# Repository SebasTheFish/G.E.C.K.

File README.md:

# Project G.E.C.K. (Garden of Eden Creation Kit)

## Overview

This project focuses around the creation of a cost-effective and flexible solution for the automation and control of various greenhouse processes.

## Goals

* Insert
* List
* Of
* Goals
* Here

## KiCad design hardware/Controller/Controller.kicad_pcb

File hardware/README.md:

# Hardware

The hardware folder can be used to store any files and documentation relating to the physical design of the hardware (gerber files, image assets, BOMs, etc.) This folder will need to be partitioned by board to keep organized.

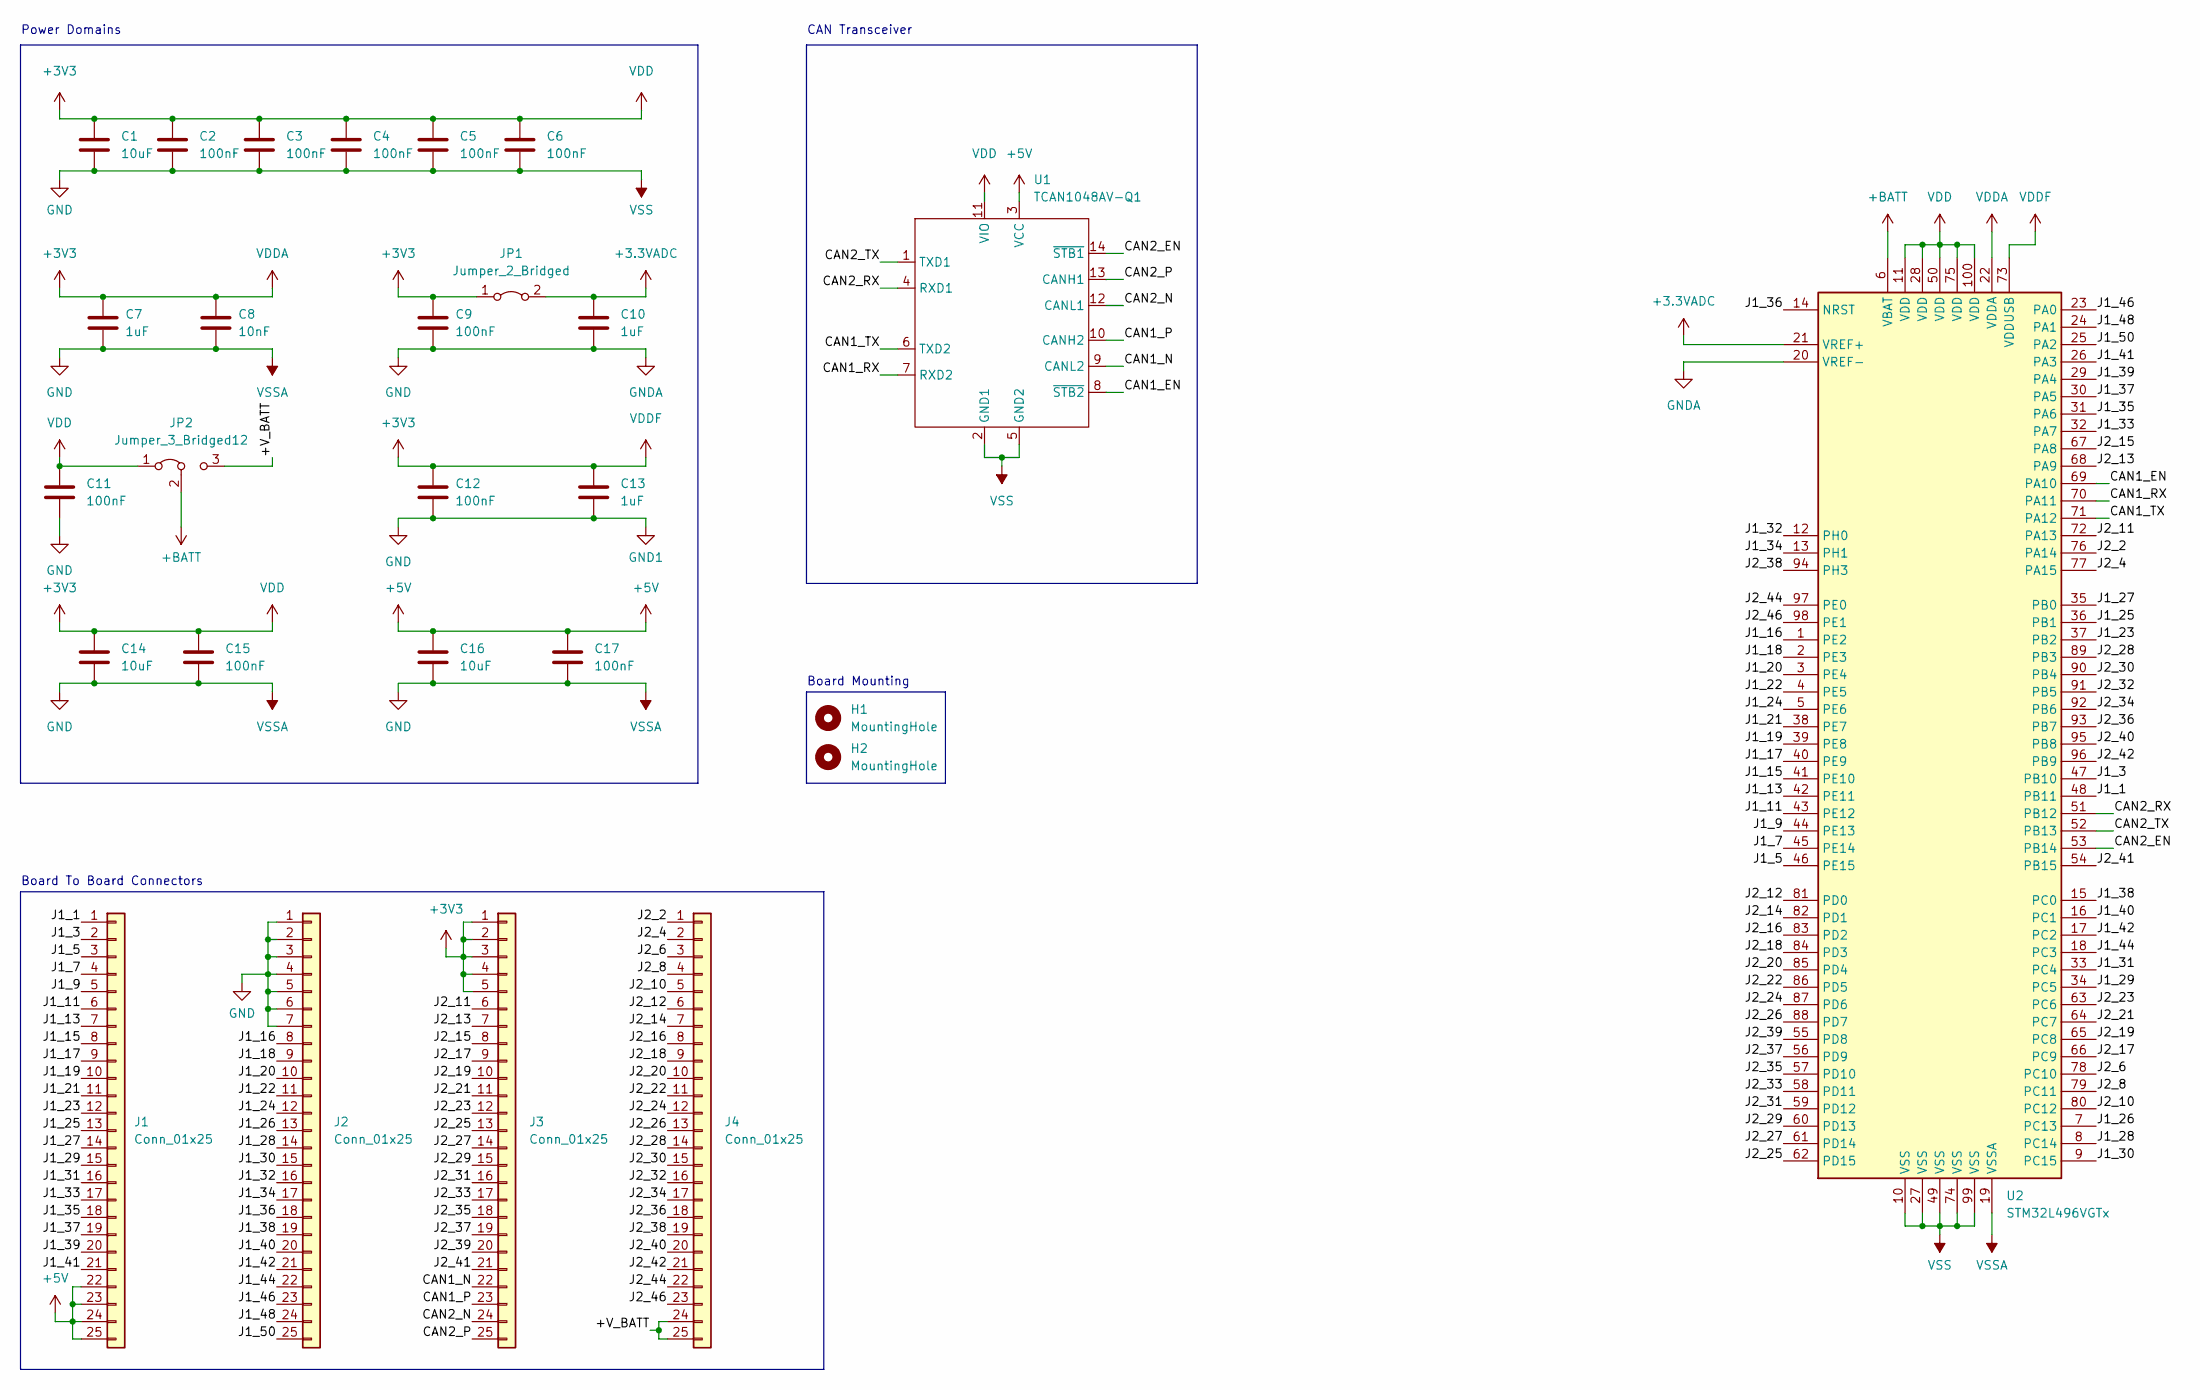
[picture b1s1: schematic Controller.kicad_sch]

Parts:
C1, C14, C16: 10uF; C_0603_1608Metric
C2, C3, C4, C5, C6, C9, C11, C12, C15, C17: 100nF; C_0603_1608Metric
C7, C10, C13: 1uF; C_0603_1608Metric
C8: 10nF; C_0603_1608Metric
H1, H2: MountingHole; MountingHole_3.2mm_M3
J1, J2, J3, J4: Conn_01x25; PinHeader_1x25_P1.00mm_Vertical
JP1: Jumper_2_Bridged; SolderJumper-2_P1.3mm_Bridged_Pad1.0x1.5mm
JP2: Jumper_3_Bridged12; SolderJumper-3_P1.3mm_Bridged12_Pad1.0x1.5mm
U1: TCAN1048AV-Q1; SOIC-14_3.9x8.7mm_P1.27mm
U2: STM32L496VGTx; LQFP-100_14x14mm_P0.5mm

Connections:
+3.3VADC: C10.1, JP1.2 (B), U2.21 (VREF+)
+5V: C16.1, C17.1, J1.22, J1.23, J1.24, J1.25, U1.3 (VCC)
+BATT: JP2.2 (C), U2.6 (VBAT)
/+V_BATT: J4.24, J4.25, JP2.3 (B)
/CAN1_EN: U1.8 (~STB2), U2.69 (PA10)
/CAN1_N: J3.22, U1.9 (CANL2)
/CAN1_P: J3.23, U1.10 (CANH2)
/CAN1_RX: U1.7 (RXD2), U2.70 (PA11)
/CAN1_TX: U1.6 (TXD2), U2.71 (PA12)
/CAN2_EN: U1.14 (~STB1), U2.53 (PB14)
/CAN2_N: J3.24, U1.12 (CANL1)
/CAN2_P: J3.25, U1.13 (CANH1)
/CAN2_RX: U1.4 (RXD1), U2.51 (PB12)
/CAN2_TX: U1.1 (TXD1), U2.52 (PB13)
/J1_1: J1.1, U2.48 (PB11)
/J1_3: J1.2, U2.47 (PB10)
/J1_5: J1.3, U2.46 (PE15)
/J1_7: J1.4, U2.45 (PE14)
/J1_9: J1.5, U2.44 (PE13)
/J1_11: J1.6, U2.43 (PE12)
/J1_13: J1.7, U2.42 (PE11)
/J1_15: J1.8, U2.41 (PE10)
/J1_16: J2.8, U2.1 (PE2)
/J1_17: J1.9, U2.40 (PE9)
/J1_18: J2.9, U2.2 (PE3)
/J1_19: J1.10, U2.39 (PE8)
/J1_20: J2.10, U2.3 (PE4)
/J1_21: J1.11, U2.38 (PE7)
/J1_22: J2.11, U2.4 (PE5)
/J1_23: J1.12, U2.37 (PB2)
/J1_24: J2.12, U2.5 (PE6)
/J1_25: J1.13, U2.36 (PB1)
/J1_26: J2.13, U2.7 (PC13)
/J1_27: J1.14, U2.35 (PB0)
/J1_28: J2.14, U2.8 (PC14)
/J1_29: J1.15, U2.34 (PC5)
/J1_30: J2.15, U2.9 (PC15)
/J1_31: J1.16, U2.33 (PC4)
/J1_32: J2.16, U2.12 (PH0)
/J1_33: J1.17, U2.32 (PA7)
/J1_34: J2.17, U2.13 (PH1)
/J1_35: J1.18, U2.31 (PA6)
/J1_36: J2.18, U2.14 (NRST)
/J1_37: J1.19, U2.30 (PA5)
/J1_38: J2.19, U2.15 (PC0)
/J1_39: J1.20, U2.29 (PA4)
/J1_40: J2.20, U2.16 (PC1)
/J1_41: J1.21, U2.26 (PA3)
/J1_42: J2.21, U2.17 (PC2)
/J1_44: J2.22, U2.18 (PC3)
/J1_46: J2.23, U2.23 (PA0)
/J1_48: J2.24, U2.24 (PA1)
/J1_50: J2.25, U2.25 (PA2)
/J2_2: J4.1, U2.76 (PA14)
/J2_4: J4.2, U2.77 (PA15)
/J2_6: J4.3, U2.78 (PC10)
/J2_8: J4.4, U2.79 (PC11)
/J2_10: J4.5, U2.80 (PC12)
/J2_11: J3.6, U2.72 (PA13)
/J2_12: J4.6, U2.81 (PD0)
/J2_13: J3.7, U2.68 (PA9)
/J2_14: J4.7, U2.82 (PD1)
/J2_15: J3.8, U2.67 (PA8)
/J2_16: J4.8, U2.83 (PD2)
/J2_17: J3.9, U2.66 (PC9)
/J2_18: J4.9, U2.84 (PD3)
/J2_19: J3.10, U2.65 (PC8)
/J2_20: J4.10, U2.85 (PD4)
/J2_21: J3.11, U2.64 (PC7)
/J2_22: J4.11, U2.86 (PD5)
/J2_23: J3.12, U2.63 (PC6)
/J2_24: J4.12, U2.87 (PD6)
/J2_25: J3.13, U2.62 (PD15)
/J2_26: J4.13, U2.88 (PD7)
/J2_27: J3.14, U2.61 (PD14)
/J2_28: J4.14, U2.89 (PB3)
/J2_29: J3.15, U2.60 (PD13)
/J2_30: J4.15, U2.90 (PB4)
/J2_31: J3.16, U2.59 (PD12)
/J2_32: J4.16, U2.91 (PB5)
/J2_33: J3.17, U2.58 (PD11)
/J2_34: J4.17, U2.92 (PB6)
/J2_35: J3.18, U2.57 (PD10)
/J2_36: J4.18, U2.93 (PB7)
/J2_37: J3.19, U2.56 (PD9)
/J2_38: J4.19, U2.94 (PH3)
/J2_39: J3.20, U2.55 (PD8)
/J2_40: J4.20, U2.95 (PB8)
/J2_41: J3.21, U2.54 (PB15)
/J2_42: J4.21, U2.96 (PB9)
/J2_44: J4.22, U2.97 (PE0)
/J2_46: J4.23, U2.98 (PE1)
GND: C1.2, C2.2, C3.2, C4.2, C5.2, C6.2, C7.2, C8.2, C9.2, C10.2, C11.2, C12.2, C13.2, C14.2, C15.2, C16.2, C17.2, J2.1, J2.2, J2.3, J2.4, J2.5, J2.6, J2.7, U1.2 (GND1), U1.5 (GND2), U2.10 (VSS), U2.19 (VSSA), U2.20 (VREF-), U2.27 (VSS), U2.49 (VSS), U2.74 (VSS), U2.99 (VSS)

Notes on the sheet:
CAN Transceiver
Board Mounting
Power Domains
Board To Board Connectors

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
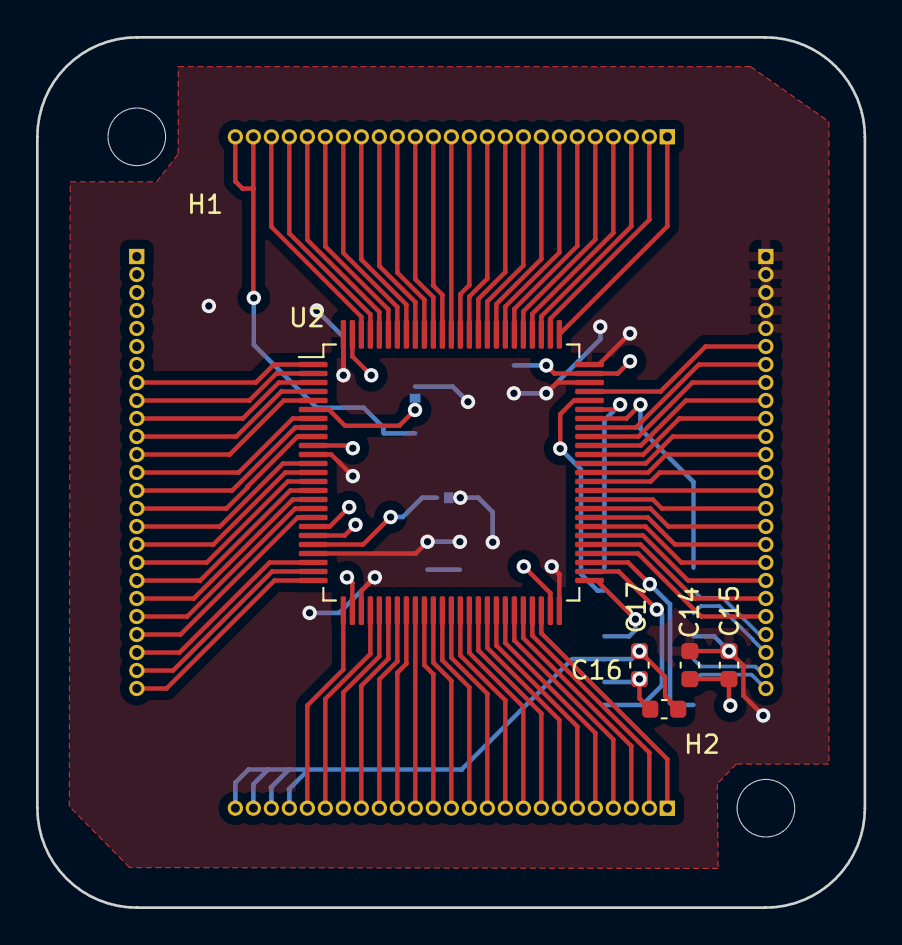
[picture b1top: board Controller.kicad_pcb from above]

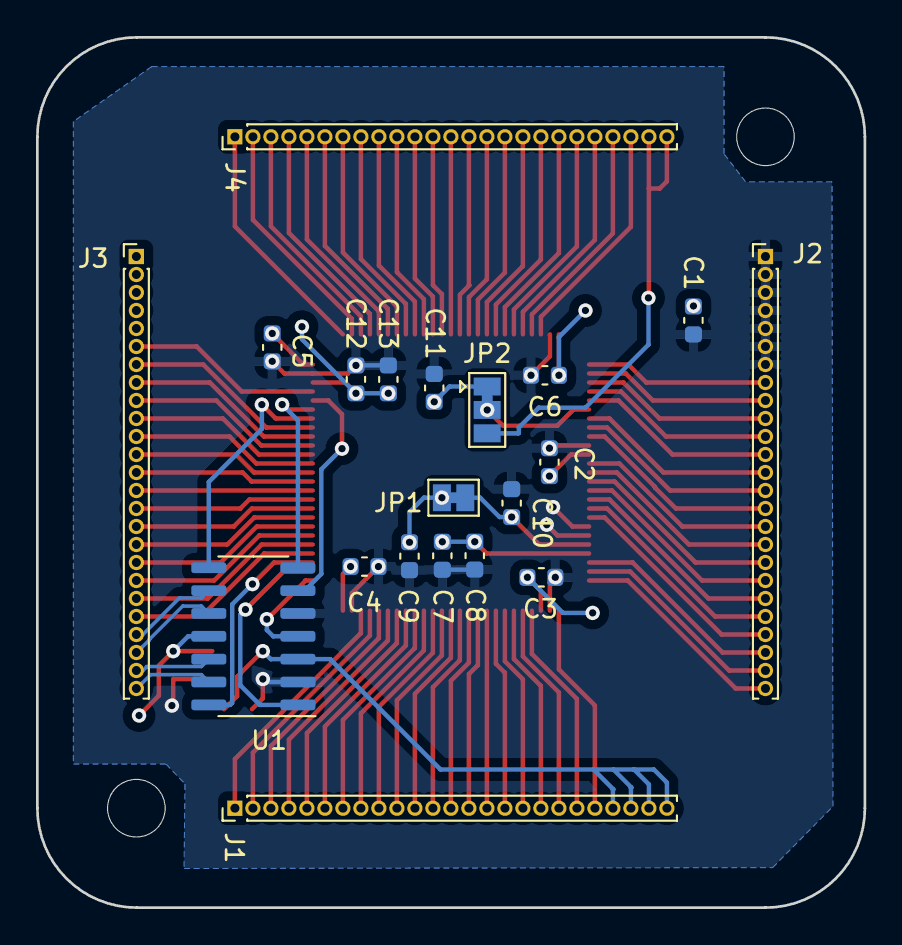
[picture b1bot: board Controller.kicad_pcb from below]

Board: 2 copper layers, 46.0 x 48.4 mm, 27 parts (20 on the bottom side), 94 nets.

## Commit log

2022-08-25 Created initial repository structure
2022-10-26 Controller board finished
2022-10-26 Re-ran the power pours
